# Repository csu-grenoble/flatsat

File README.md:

# Easy-Space Flatsat  📡 🚀 extensions

Extensions to [Easy Space](https://www.easy-space.fr/) INISAT flatsat mockup

## [Board #1: ThingSat @ INISAT](Hardware/Thingsat_INISAT)  📡 🚀 (OBC + LoRa Gateway + CAN Bus)

* 1x [ST Nucleo L432KC](https://www.st.com/en/evaluation-tools/nucleo-l432kc.html)
* 1x [RAK Wireless RAK5146 (all bands)](https://store.rakwireless.com/products/wislink-concentrator-module-sx1303-rak5146-lorawan?_pos=1&_sid=c9dc2f56d&_ss=r&variant=39667784908998)
* 1x Mikrobus slots for homebrew LoRa click boards (Lambda80, GNSS RTK) or [others click boards](https://www.mikroe.com/shop)
* 3x [Groove connectors](https://wiki.seeedstudio.com/Grove_System/)
* 1x [ST L9616 Automotive High Speed Can Bus Transceiver](https://www.st.com/en/automotive-analog-and-power/l9616.html)

## [Board #2 ESP32 TinyGS](Hardware/2U-PCB-TinyGS)

* 1x [ESP32 Wroom](https://www.espressif.com/en/products/devkits)
* 2x Mikrobus slots for homebrew LoRa click boards (Lambda80, RN2483) or [others click boards](https://www.mikroe.com/shop)
* 6x [Groove connectors](https://wiki.seeedstudio.com/Grove_System/)
* 1x [ST L9616 Automotive High Speed Can Bus Transceiver](https://www.st.com/en/automotive-analog-and-power/l9616.html)

See [TinyGS 2G4 Station](https://github.com/thingsat/tinygs_2g4station)

## Board #3 Nucleo L476RG

* 1x [Nucleo L476RG](https://www.st.com/en/evaluation-tools/nucleo-l476rg.html)
* 1x [ST L9616 Automotive High Speed Can Bus Transceiver](https://www.st.com/en/automotive-analog-and-power/l9616.html)

## References

* [EasySpace Diffusion](https://github.com/EasySpace-Diffusion)
* [TinyGS 2G4 Station](https://github.com/thingsat/tinygs_2g4station)

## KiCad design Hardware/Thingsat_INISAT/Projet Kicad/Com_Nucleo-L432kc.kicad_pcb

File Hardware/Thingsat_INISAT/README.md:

# **Carte Thingsat @ INISAT 📡 🚀 : OBC + Communication avec Nucleo L432KC + Gateway RAK5146**

La carte [Thingsat](https://gricad-gitlab.univ-grenoble-alpes.fr/thingsat/public/-/blob/master/README.md?ref_type=heads) @ INISAT a pour but de fonctionner comme un OBC qui peut se relier à l'environnement INISAT grace au header standardisé. 

Cette carte fonctionne également comme une carte de communication avancée LoRa/FSK avec l'ajout d'un module [gateway LoRa (+ GNSS) au format mini-PCIe](https://www.mikroe.com/mikrobus) comme le module [RAK5146](../../Hardware/sx1302_modules).

> Remarque: D'autres modules gateways LoRa avec ou sans module GNSS sont compatibles avec la carte. Voir la [liste](../../Hardware/sx1302_modules).

Cette carte peut accueillir un module MikroBus qui peut accueillir des platines de l'[écosystème Mikrobus](https://www.mikroe.com/mikrobus).

Cette carte peut accueillir trois platines Grove I2C situés sous le module mini-PCIe .

La carte [Thingsat](https://gricad-gitlab.univ-grenoble-alpes.fr/thingsat/public/-/blob/master/README.md?ref_type=heads) @ INISAT peut être utilisée seule (standalone) pour des expérimentations à bord de [ballons stratosphériques](https://gricad-gitlab.univ-grenoble-alpes.fr/thingsat/public/-/blob/master/balloons/README.md).

## Schématique

[Schematic](schematic.pdf)

## Firmware

Le firmware avec RIOT OS est disponible [ici](../../Software/riot).

Le firmware avec [ici](../../Software/arduino) est à l'étude.

## Montages

La carte peut être montée en deux versions:

**Carte avec 1 connecteur mini-PCI-Express (pour accueillir un concentrateur LoRa) et 1 support Mikrobus**

**Carte avec 3 connecteurs Grove et 1 support Mikrobus**

## OpenLog

Pour journaliser la console d'exécution du firmware de la carte Nucleo L432KC, vous pouvez ajouter une [platine OpenLog](https://github.com/CampusIoT/tutorial/tree/master/openlogger) sur les headers externes de la carte.

| OpenLog | Nucleo L432KC |
| ------- | ------------- |
| `3V3` | `3V3` (et non `VIN`) |
| `GND` | `GND` |
| `RXI` | `A7` (aka `UART2_TX`) | 

> NB: il est recommandé que le port console soit configuré à 9600 bauds pour éviter la perte de caratères lors de l'écriture sur la carte SD. Pour les firmwares avec RIOT OS, il faut redéfinir dans le Makefile `STDIO_UART_BAUDRATE` avec `CFLAGS += -DSTDIO_UART_BAUDRATE=9600`

## Description de la carte
La carte est equipée de:

 - Un emplacement pour carte **Nucleo-32** (ou arduino nano)
 - Un emplacement **MikroBus**
 - Un connecteur **mini-PCI-Express** OU 3 connecteurs **Grove** I2C (en fonction de la version de la carte)
 - Un connecteur **Inisat** (pour se raccorder aux autres cartes de l'ecosystème Inisat)
 - Un **transceiver CAN** ([L9616](https://www.st.com/en/automotive-analog-and-power/l9616.html) - STMicroelectronics)
 - Un **capteur de température** I2C ([MCP9808](https://www.microchip.com/en-us/product/mcp9808#document-table) - Microchip)

## Nucleo 32 (L432KC)

## Emplacement MikroBus

## Connecteur mini PCI Express

## [Modules SX1302/3 compatibles](../sx1302_modules)

* [x] RAK5146 Gateway Concentrator Module for LoRaWAN SPI
* [ ] RAK2287 WisLink LPWAN Concentrator SPI (to test)
* [x] Nebra NBR-0094
* [x] Seeedstudio Wio-WM1303 Long Range Gateway Module
* [ ] Seeedstudio Wio-WM1302 Long Range Gateway Module  (to test)
* [ ] Heltec HT1303  (to test)

## Jumpers de selection des signaux

Les signaux marqués d'une étoile sur les diagrammes sont partagées entre plusieurs empreintes.
Pour pouvoir utiliser ces signaux il faut donc les "router" vers l'emplacement dont on veut se servir en plaçant correctement les jumpers en bas à droite de la carte.

- PWM1 : 
	- position haute: `PWM Mikrobus` 	(pin 8 de l'empreinte Mikrobus)
	- position basse: `PWM Inisat` 		(pin 6 du connecteur Inisat)
	
- INT :
	- position haute: `INT Mikrobus` 	(pin 7 de l'empreinte Mikrobus)
	- position basse: `PPS Lora core` 	(pin 19 du connecteur mini PCI Express)
	
- UART (Rx et Tx) :
	- position haute: `UART Mikrobus` 	(pin 5 et 6 de l'empreinte Mikrobus)
	- position basse: `UART GPS Lora core` (pin 31 et 33 du connecteur mini PCI Express)

## Transceiver CAN

Le transceiver CAN peut être configuré pour opérations à hautes vitesses (> 250KBaud/s) ou à basse vitesse (< 250KBaud/s).
Pour positionner le transceiver en mode haute vitesse, il faut placer un jumper sur le connecteur `JP2`.

## Capteur de temperature [MPC9808](https://www.microchip.com/en-us/product/mcp9808#document-table)

L'adresse i2c du capteur de température est définie comme suit : `0b 0 0 1 1 A2 A1 A0`
les bits de poids faibles A2,A1 et A0 sont définis en plaçant des résistances 0 Ohms (_il ne faut donc placer qu'une seule résistance pour chaque bit_): 

## Modularité de la carte

Les composants entourés d'un rectangle en pointillé ne doivent pas necessairement être montées. Cela dépend de l'usage de la carte. Voici les composants concernés:

* Alimentation Nucleo
	* `R7`: alimentation de la nucleo en 5V (_nécessaire si la carte Inisat est utilisé seule **ET** que l'on a besoin d'utiliser le 5V pour le Mikrobus_)
	* `R6`: alimentation de la nucleo en 3.3V (_nécessaire si la carte Inisat est utilisé seule_)
* Alimentation Transceiver CAN
	* `R9`: alimentation L9616 en 5V
	* `R8`: alimentation L9616 en 3.3V (_par défaut_)
* Selection adresse i2c capteur de temperature (`R10`-`R15`)
	* [voir ci-dessus](#capteur-de-temperature)

# Contributeurs

* Léo CORDIER (Design PCB + montage)
* Vincent Grennerat (Design PCB)
* Didier Donsez (firmware de test)
* [Lucas ORLANDO BERNARDES](https://www.linkedin.com/in/lucas-orlando-bernardes-1b7397256/) (initial design)

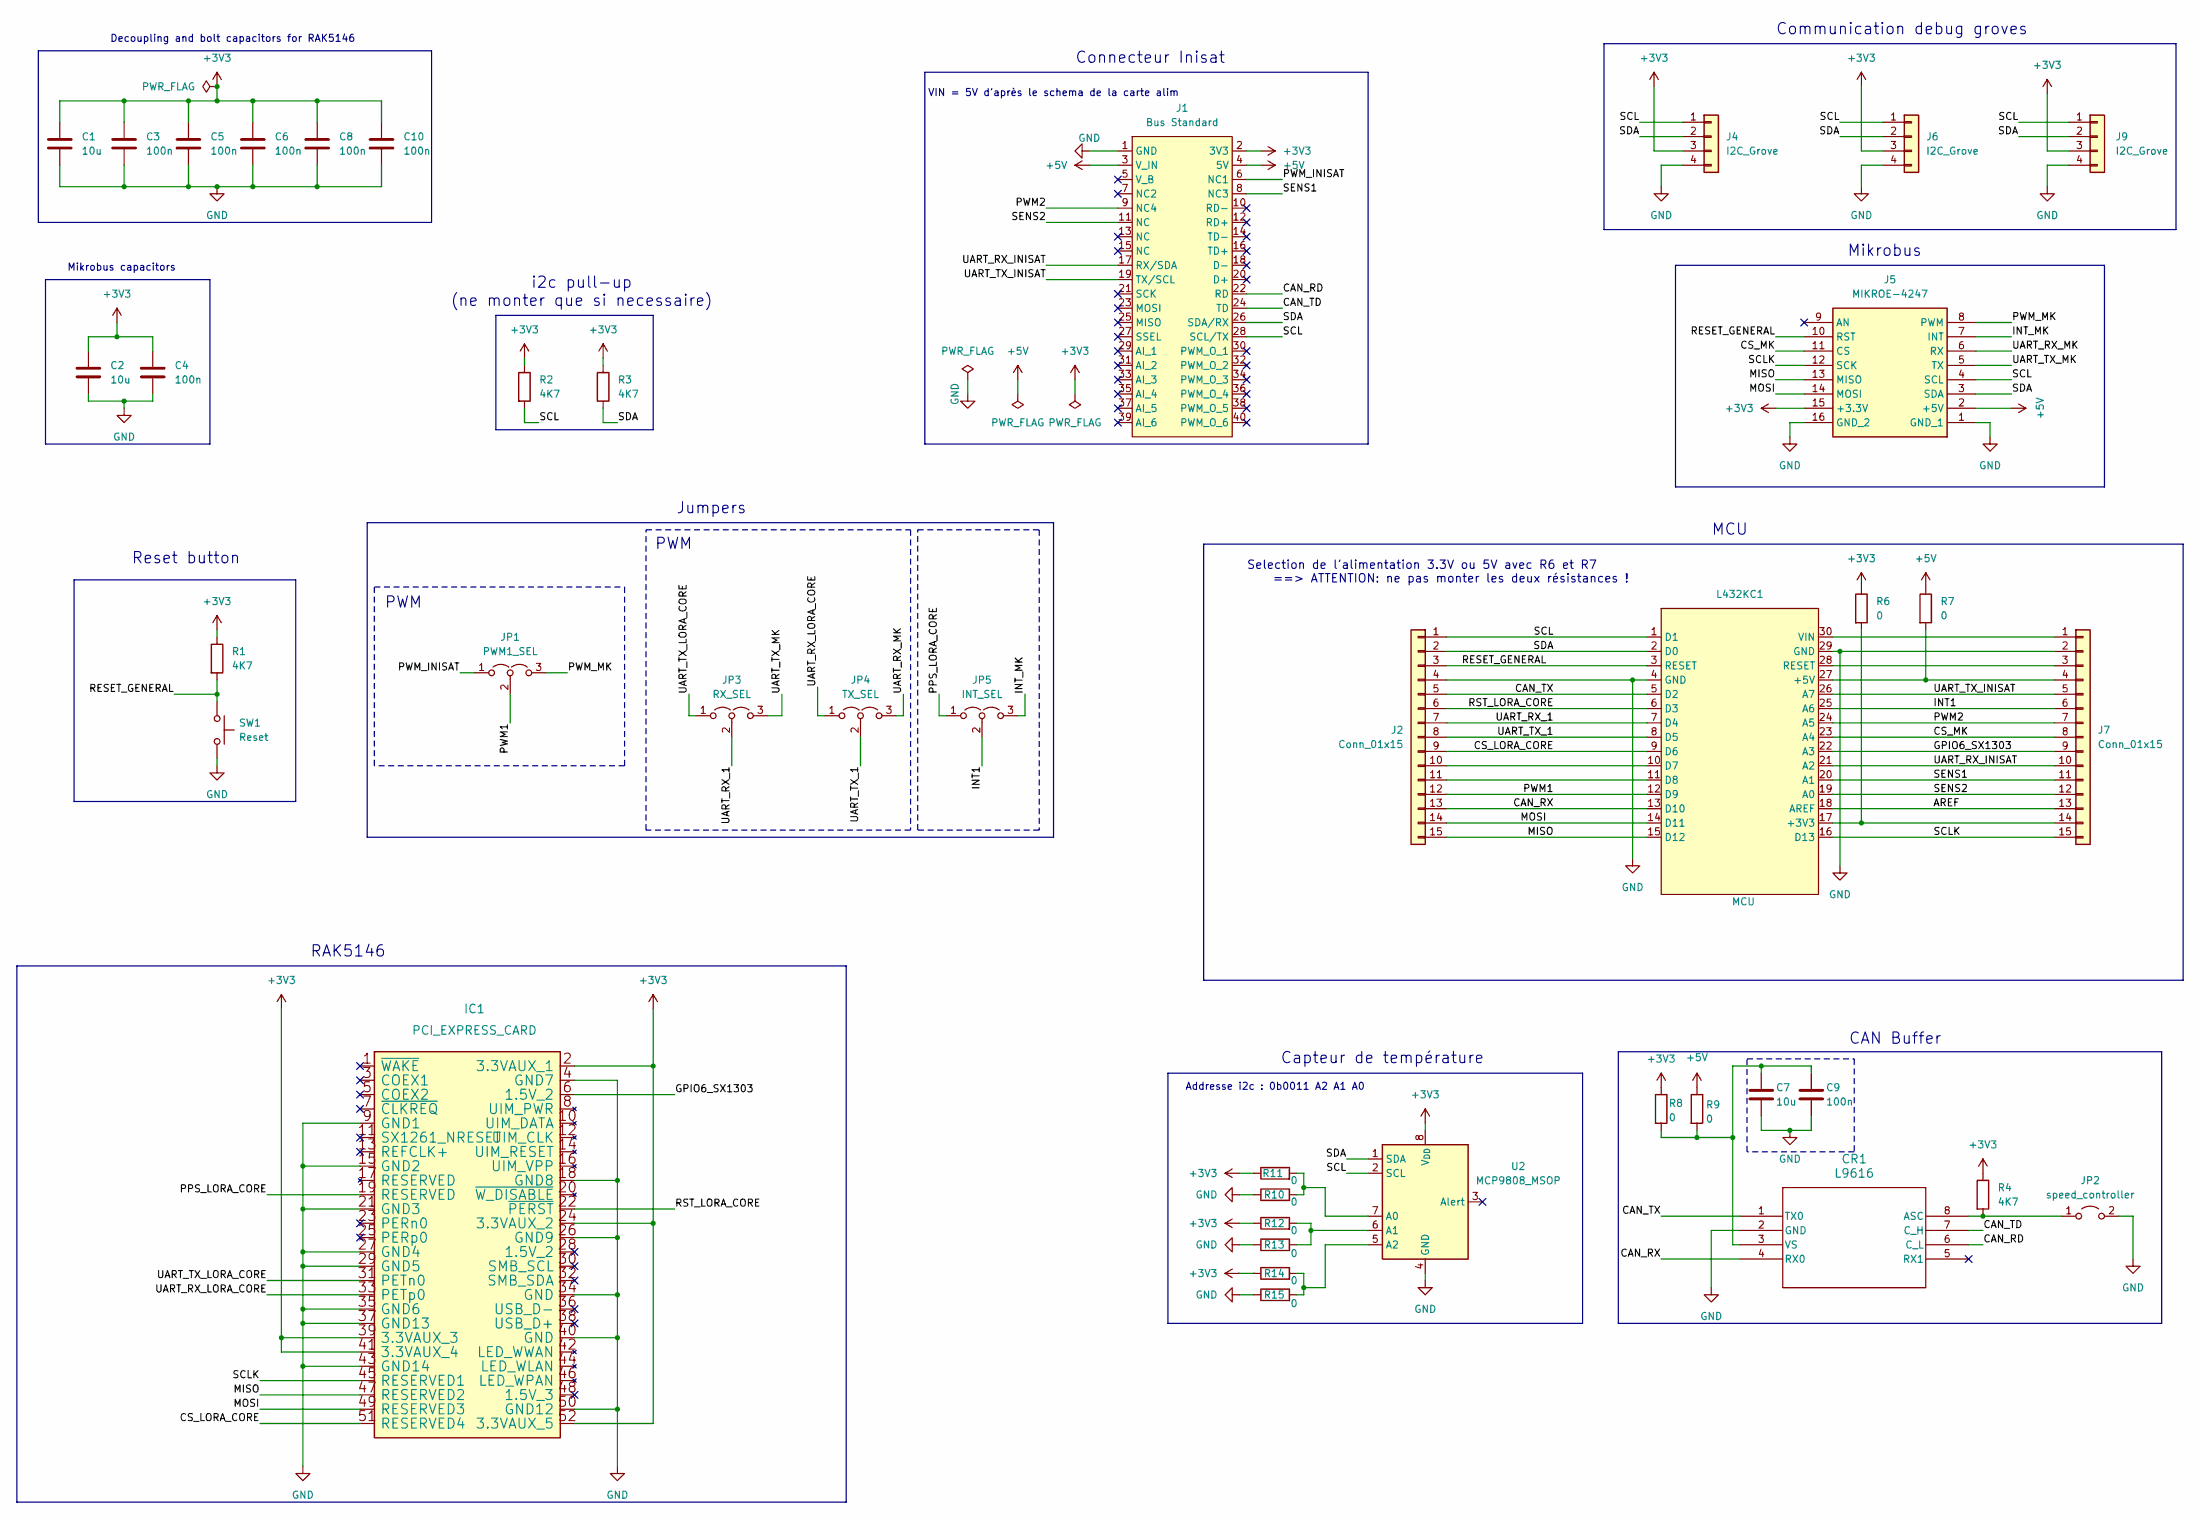
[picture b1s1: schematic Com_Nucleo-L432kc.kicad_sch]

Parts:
C1, C2, C7: 10u; C_0805_2012Metric_Pad1.18x1.45mm_HandSolder
C3, C4, C5, C6, C8, C9, C10: 100n; C_0805_2012Metric_Pad1.18x1.45mm_HandSolder
CR1: L9616; SO-8_3.9x4.9mm_P1.27mm
IC1: PCI_EXPRESS_CARD; BUS_PCI_Express_Mini
J1: Bus Standard; flatsat_conn
J2, J7: Conn_01x15; PinHeader_1x15_P2.54mm_Vertical
J4, J6, J9: I2C_Grove; NS-Tech_Grove_1x04_P2mm_Vertical
J5: MIKROE-4247; MIKROE4247; Manufacturer_Part_Number MIKROE-4247; Mouser Part Number 932-MIKROE-4247
JP1: PWM1_SEL; PinHeader_1x03_P2.54mm_Vertical
JP2: speed_controller; PinHeader_1x02_P2.54mm_Vertical
JP3: RX_SEL; PinHeader_1x03_P2.54mm_Vertical
JP4: TX_SEL; PinHeader_1x03_P2.54mm_Vertical
JP5: INT_SEL; PinHeader_1x03_P2.54mm_Vertical
L432KC1: MCU; Arduino_Nano
R1, R2, R3, R4: 4K7; R_0805_2012Metric_Pad1.20x1.40mm_HandSolder
R6, R7, R8, R9, R10, R11, R12, R13, R14, R15: 0; R_0805_2012Metric_Pad1.20x1.40mm_HandSolder
SW1: Reset; SW_PUSH_6mm
U2: MCP9808_MSOP; MSOP-8_3x3mm_P0.65mm

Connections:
+3V3: C1.1, C2.1, C3.1, C4.1, C5.1, C6.1, C8.1, C10.1, IC1.2 (3.3VAUX_1), IC1.24 (3.3VAUX_2), IC1.39 (3.3VAUX_3), IC1.41 (3.3VAUX_4), IC1.52 (3.3VAUX_5), J1.2 (3V3), J4.3, J5.15 (+3.3V), J6.3, J9.3, R1.1, R2.1, R3.1, R4.1, R6.1, R8.1, R11.1, R12.1, R14.1, U2.8 (V_{DD})
+5V: J1.3 (V_IN), J1.4 (5V), J5.2 (+5V), R7.1, R9.1
/AREF: J7.13, L432KC1.18 (AREF)
/CAN_RD: CR1.6 (C_L), J1.22 (RD)
/CAN_RX: CR1.4 (RX0), J2.13, L432KC1.13 (D10)
/CAN_TD: CR1.7 (C_H), J1.24 (TD)
/CAN_TX: CR1.1 (TX0), J2.5, L432KC1.5 (D2)
/CS_LORA_CORE: IC1.51 (RESERVED4), J2.9, L432KC1.9 (D6)
/CS_MK: J5.11 (CS), J7.8, L432KC1.23 (A4)
/GPIO6_SX1303: IC1.6 (1.5V_2), J7.9, L432KC1.22 (A3)
/INT1: J7.6, JP5.2 (C), L432KC1.25 (A6)
/INT_MK: J5.7 (INT), JP5.3 (B)
/MISO: IC1.47 (RESERVED2), J2.15, J5.13 (MISO), L432KC1.15 (D12)
/MOSI: IC1.49 (RESERVED3), J2.14, J5.14 (MOSI), L432KC1.14 (D11)
/PPS_LORA_CORE: IC1.19 (RESERVED), JP5.1 (A)
/PWM1: J2.12, JP1.2 (C), L432KC1.12 (D9)
/PWM2: J1.9 (NC4), J7.7, L432KC1.24 (A5)
/PWM_INISAT: J1.6 (NC1), JP1.1 (A)
/PWM_MK: J5.8 (PWM), JP1.3 (B)
/RESET_GENERAL: J2.3, J5.10 (RST), L432KC1.3 (RESET), R1.2, SW1.1
/RST_LORA_CORE: IC1.22 (~PERST), J2.6, L432KC1.6 (D3)
/SCL: J1.28 (SCL/TX), J2.1, J4.1, J5.4 (SCL), J6.1, J9.1, L432KC1.1 (D1), R2.2, U2.2 (SCL)
/SCLK: IC1.45 (RESERVED1), J5.12 (SCK), J7.15, L432KC1.16 (D13)
/SDA: J1.26 (SDA/RX), J2.2, J4.2, J5.3 (SDA), J6.2, J9.2, L432KC1.2 (D0), R3.2, U2.1 (SDA)
/SENS1: J1.8 (NC3), J7.11, L432KC1.20 (A1)
/SENS2: J1.11 (NC), J7.12, L432KC1.19 (A0)
/UART_RX_1: J2.7, JP3.2 (C), L432KC1.7 (D4)
/UART_RX_INISAT: J1.17 (RX/SDA), J7.10, L432KC1.21 (A2)
/UART_RX_LORA_CORE: IC1.33 (PETp0), JP4.1 (A)
/UART_RX_MK: J5.6 (RX), JP4.3 (B)
/UART_TX_1: J2.8, JP4.2 (C), L432KC1.8 (D5)
/UART_TX_INISAT: J1.19 (TX/SCL), J7.5, L432KC1.26 (A7)
/UART_TX_LORA_CORE: IC1.31 (PETn0), JP3.1 (A)
/UART_TX_MK: J5.5 (TX), JP3.3 (B)
GND: C1.2, C2.2, C3.2, C4.2, C5.2, C6.2, C7.2, C8.2, C9.2, C10.2, CR1.2 (GND), IC1.4 (GND7), IC1.9 (GND1), IC1.15 (GND2), IC1.18 (GND8), IC1.21 (GND3), IC1.26 (GND9), IC1.27 (GND4), IC1.29 (GND5), IC1.34 (GND), IC1.35 (GND6), IC1.37 (GND13), IC1.40 (GND), IC1.43 (GND14), IC1.50 (GND12), J1.1 (GND), J2.4, J4.4, J5.1 (GND_1), J5.16 (GND_2), J6.4, J7.2, J9.4, JP2.2 (B), L432KC1.4 (GND), L432KC1.29 (GND), R10.1, R13.1, R15.1, SW1.2, U2.4 (GND)
unnamed: CR1.8 (ASC), JP2.1 (A), R4.2
unnamed: C7.1, C9.1, CR1.3 (VS), R8.2, R9.2
unnamed: J2.10, L432KC1.10 (D7)
unnamed: J2.11, L432KC1.11 (D8)
unnamed: J7.1, L432KC1.30 (VIN)
unnamed: J7.3, L432KC1.28 (RESET)
unnamed: J7.4, L432KC1.27 (+5V), R7.2
unnamed: J7.14, L432KC1.17 (+3V3), R6.2
unnamed: R10.2, R11.2, U2.7 (A0)
unnamed: R12.2, R13.2, U2.6 (A1)
unnamed: R14.2, R15.2, U2.5 (A2)

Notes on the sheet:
Connecteur Inisat
Capteur de température
RAK5146
PWM
VIN = 5V d'après le schema de la carte alim
Selection de l'alimentation 3.3V ou 5V avec R6 et R7 ==> ATTENTION: ne pas monter les deux résistances !
Mikrobus capacitors
Communication debug groves
Addresse i2c : 0b0011 A2 A1 A0
Mikrobus
MCU
CAN Buffer
Jumpers
Decoupling and bolt capacitors for RAK5146
i2c pull-up (ne monter que si necessaire)
Reset button

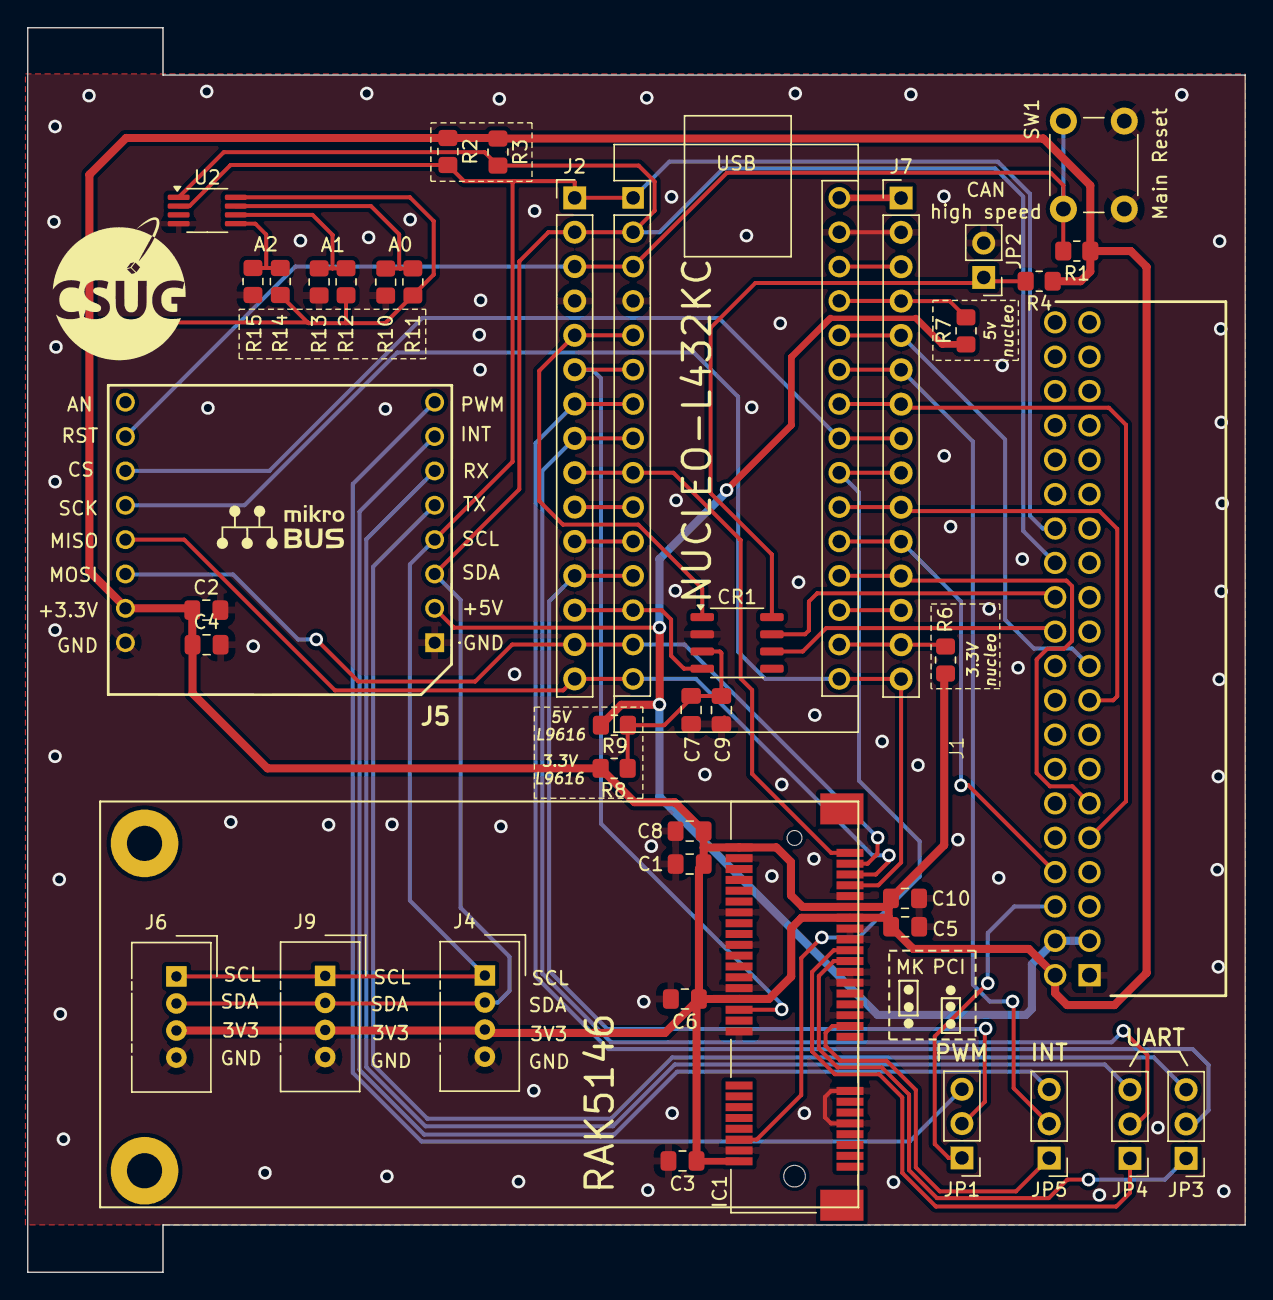
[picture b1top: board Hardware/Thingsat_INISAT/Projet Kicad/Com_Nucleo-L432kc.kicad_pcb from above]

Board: 2 copper layers, 90.0 x 92.0 mm, 42 parts (1 on the bottom side), 46 nets.

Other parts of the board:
QR: LOGO; qr_code_flatsat

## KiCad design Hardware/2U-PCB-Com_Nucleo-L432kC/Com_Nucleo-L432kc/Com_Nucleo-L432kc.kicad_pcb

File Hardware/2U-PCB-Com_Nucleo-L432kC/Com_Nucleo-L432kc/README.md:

# **Carte Thingsat @ INISAT 📡 🚀 : OBC + Communication avec Nucleo L432KC + Gateway RAK5146**

La carte [Thingsat](https://gricad-gitlab.univ-grenoble-alpes.fr/thingsat/public/-/blob/master/README.md?ref_type=heads) @ INISAT a pour but de fonctionner comme un OBC qui peut se relier à l'environnement INISAT grace au header standardisé. 

Cette carte peut accueillir un module MikroBus, trois modules Grove et une gateway LoRa RAK156 (+ GNSS).

> Remarque: D'autres modules gateways LoRa sont compatibles avec la carte. Voir la [liste](../../sx1302_modules).

Le firmware sur RIOT OS est disponible [ici](../../Software/riot).

Dotée du module gateway LoRa RAK156, elle peut également être utilisée comme la carte [Thingsat](https://gricad-gitlab.univ-grenoble-alpes.fr/thingsat/public/-/blob/master/README.md?ref_type=heads) @ INISAT.

La carte peut être montée en deux versions:

**Carte avec 1 connecteur mini-PCI-Express (pour accueillir un concentrateur LoRa) et 1 support Mikrobus**

**Carte avec 3 connecteurs Grove et 1 support Mikrobus**

## Description de la carte
La carte est equipée de:

 - Un emplacement pour carte **Nucleo-32** (ou arduino nano)
 - Un emplacement **MikroBus**
 - Un connecteur **mini-PCI-Express** OU 3 connecteurs **Grove** I2C (en fonction de la version de la carte)
 - Un connecteur **Inisat** (pour se raccorder aux autres cartes de l'ecosystème Inisat)
 - Un **transceiver CAN** ([L9616](https://www.st.com/en/automotive-analog-and-power/l9616.html) - STMicroelectronics)
 - Un **capteur de température** I2C ([MCP9808](https://www.microchip.com/en-us/product/mcp9808#document-table) - Microchip)

## Nucleo 32 (L432KC)

## Emplacement MikroBus

## mini PCI Express

## Jumpers de selection des signaux
Les signaux marqués d'une étoile sur les diagrammes sont partagées entre plusieurs empreintes.
Pour pouvoir utiliser ces signaux il faut donc les "router" vers l'emplacement dont on veut se servir en plaçant correctement les jumpers en bas à droite de la carte.

- PWM1 : 
	- position haute: `PWM Mikrobus` 		(pin 8 de l'empreinte Mikrobus)
	- position basse: `PWM Inisat` 		(pin 6 du connecteur Inisat)
	
- INT :
	- position haute: `INT Mikrobus` 		(pin 7 de l'empreinte Mikrobus)
	- position basse: `PPS Lora core` 	(pin 19 du connecteur mini PCI Express)
	
- UART (Rx et Tx) :
	- position haute: `UART Mikrobus` 	(pin 5 et 6 de l'empreinte Mikrobus)
	- position basse: `UART GPS Lora core` (pin 31 et 33 du connecteur mini PCI Express)

## Transceiver CAN
Le transceiver CAN peut être configuré pour opérations à hautes vitesses (> 250KBaud/s) ou à basse vitesse (< 250KBaud/s).
Pour positionner le transceiver en mode haute vitesse, il faut placer un jumper sur le connecteur `JP2`.

## Capteur de temperature
L'adresse i2c du capteur de température est définie comme suit : `0b 0 0 1 1 A2 A1 A0`
les bits de poids faibles A2,A1 et A0 sont définis en plaçant des résistances 0 Ohms (_il ne faut donc placer qu'une seule résistance pour chaque bit_): 

## Modularité de la carte
Les composants entourés d'un rectangle en pointillé ne doivent pas necessairement être montées. Cela dépend de l'usage de la carte. Voici les composants concernés:

* Alimentation Nucleo
	* `R7`: alimentation de la nucleo en 5V (_nécessaire si la carte Inisat est utilisé seule **ET** que l'on a besoin d'utiliser le 5V pour le Mikrobus_)
	* `R6`: alimentation de la nucleo en 3.3V (_nécessaire si la carte Inisat est utilisé seule_)
* Alimentation Transceiver CAN
	* `R9`: alimentation L9616 en 5V
	* `R8`: alimentation L9616 en 3.3V (_par défaut_)
* Selection adresse i2c capteur de temperature (`R10`-`R15`)
	* [voir ci-dessus](#capteur-de-temperature)

# Contributeurs

* Léo CORDIER (Design PCB + montage)
* Vincent Grennerat (Design PCB)
* Didier Donsez (firmware de test)

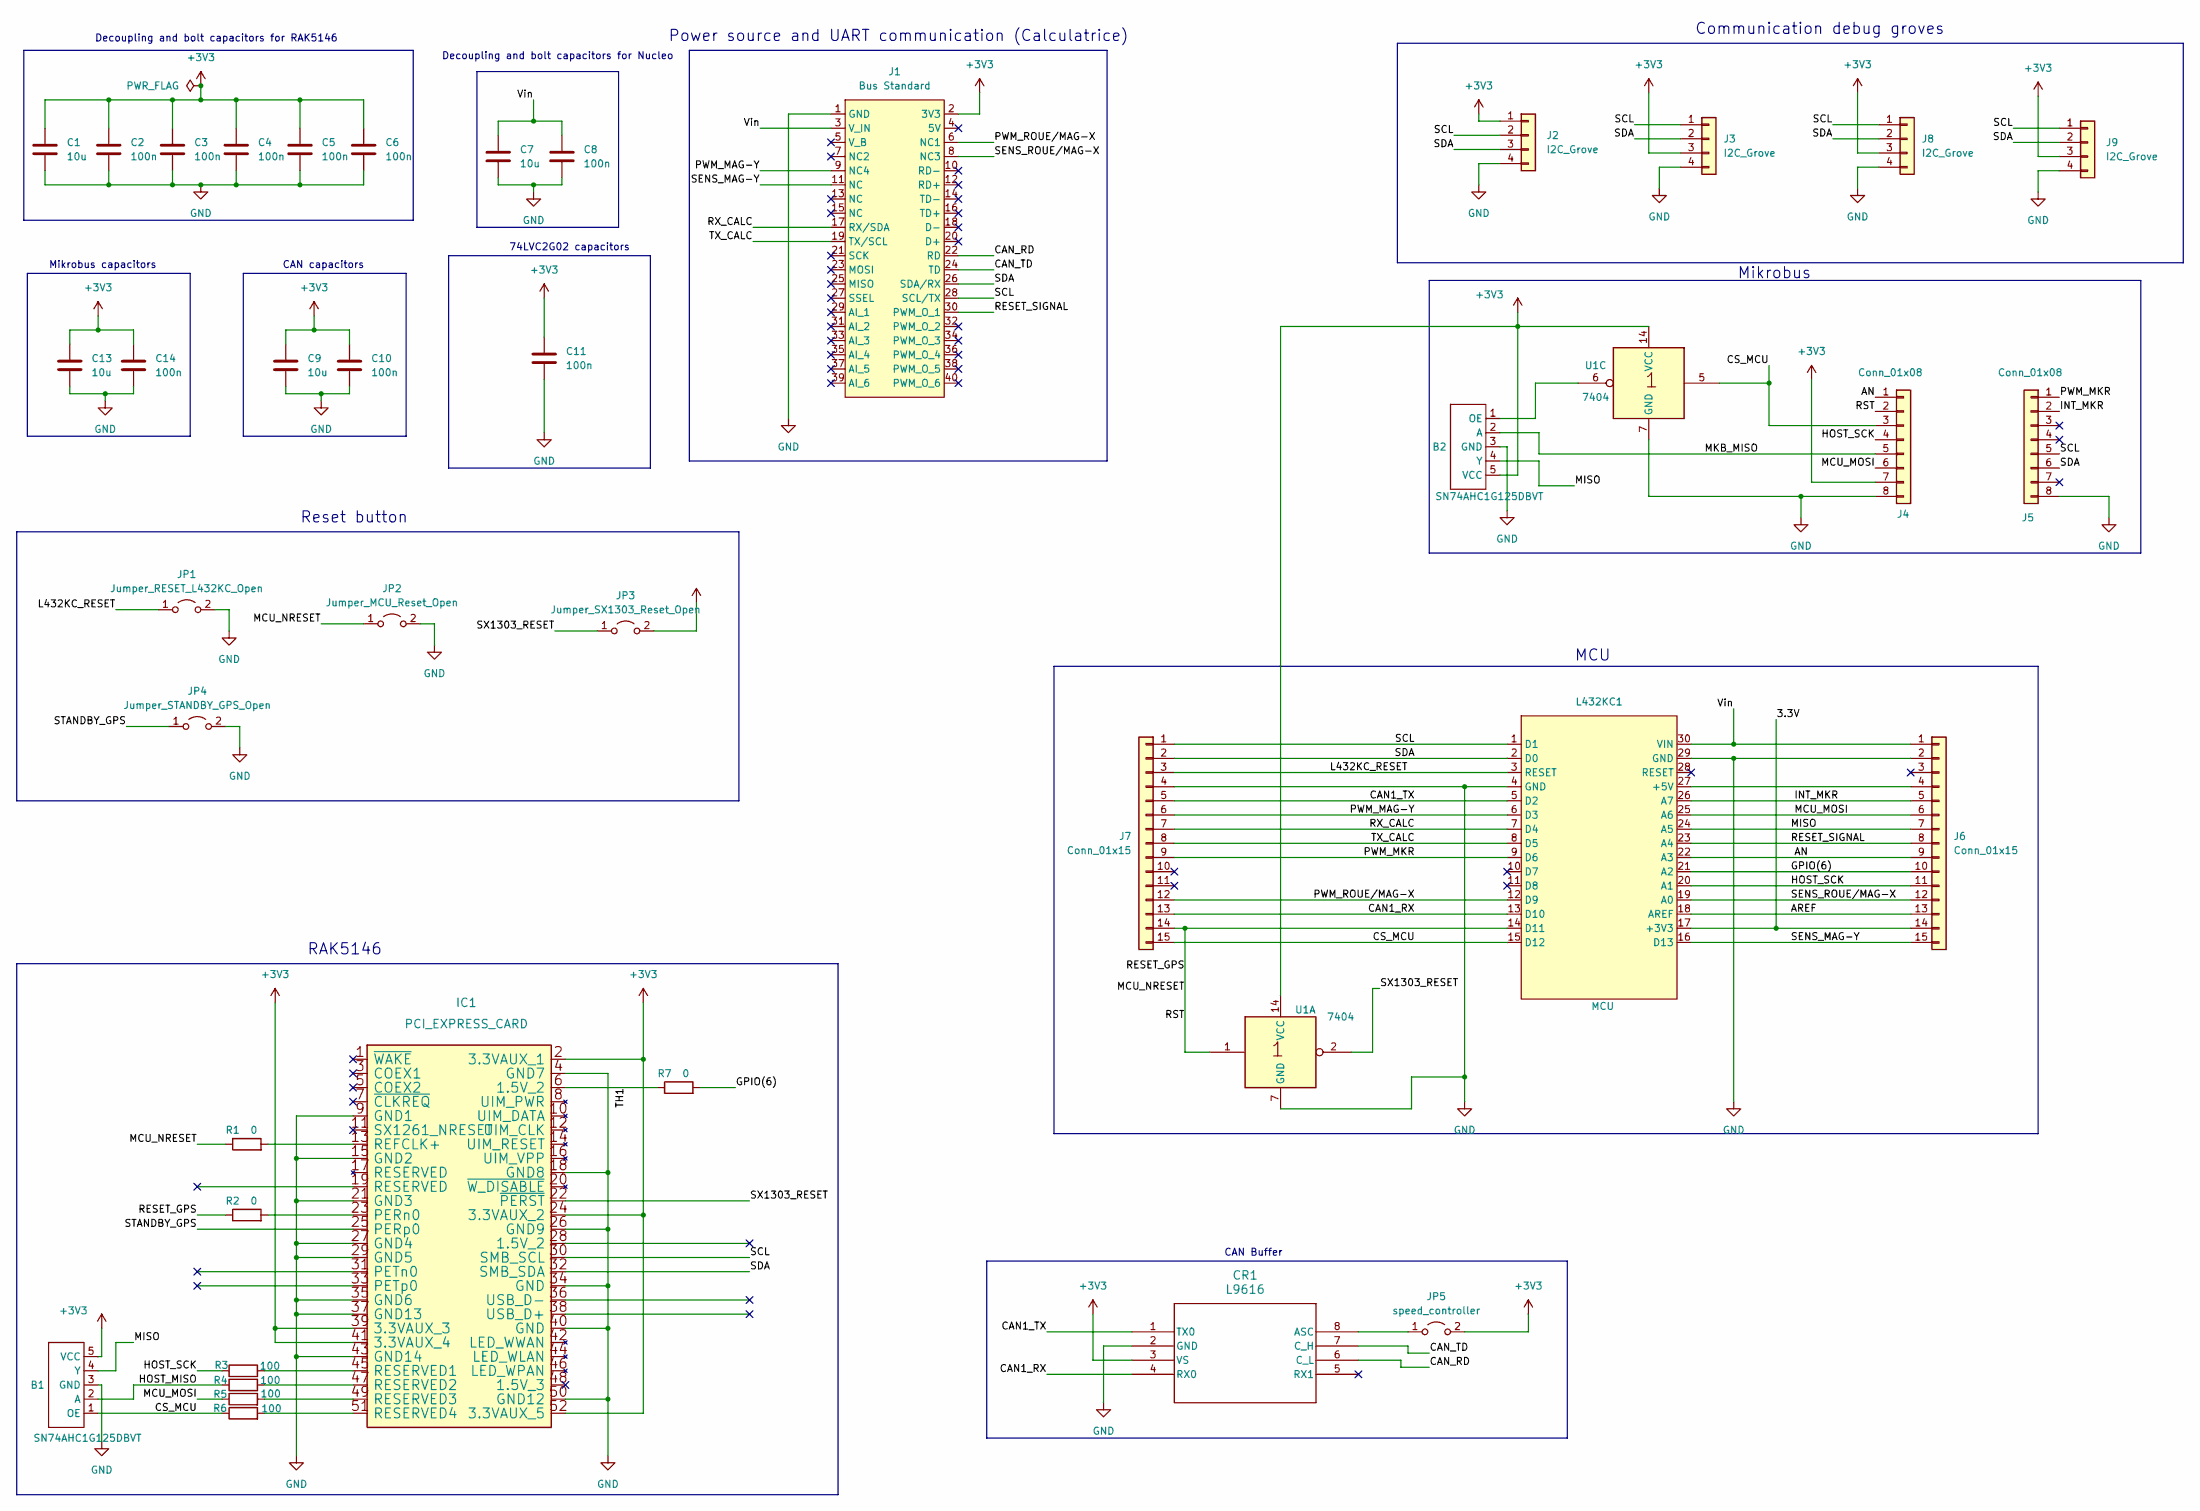
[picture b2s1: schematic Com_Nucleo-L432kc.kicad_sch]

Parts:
B1, B2: SN74AHC1G125DBVT; TSOP-5_1.65x3.05mm_P0.95mm
C1, C7, C9, C13: 10u; C_0805_2012Metric
C2, C3, C4, C5, C6, C8, C10, C11, C14: 100n; C_0805_2012Metric
CR1: L9616; SO-8_STM
IC1: PCI_EXPRESS_CARD; BUS_PCI_Express_Mini
J1: Bus Standard; flatsat_conn
J2: I2C_Grove; PinSocket_1x04_P2.54mm_Vertical
J3, J8, J9: I2C_Grove; NS-Tech_Grove_1x04_P2mm_Vertical
J4, J5: Conn_01x08; MIkrobus_Connector
J6, J7: Conn_01x15; PinSocket_1x15_P2.54mm_Vertical
JP1: Jumper_RESET_L432KC_Open; SW_Push_1P1T_NO_CK_KMR2
JP2: Jumper_MCU_Reset_Open; SW_Push_1P1T_NO_CK_KMR2
JP3: Jumper_SX1303_Reset_Open; SW_Push_1P1T_NO_CK_KMR2
JP4: Jumper_STANDBY_GPS_Open; PinHeader_1x02_P2.54mm_Vertical
JP5: speed_controller; PinHeader_1x02_P2.54mm_Vertical
L432KC1: MCU; Arduino_Nano
R1, R2, R7: 0; R_0805_2012Metric
R3, R4, R5, R6: 100; R_0805_2012Metric
U1: 7404; N14

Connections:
+3V3: B1.5 (VCC), B2.5 (VCC), C1.1, C2.1, C3.1, C4.1, C5.1, C6.1, C9.1, C10.1, C11.1, C13.1, C14.1, CR1.3 (VS), IC1.2 (3.3VAUX_1), IC1.24 (3.3VAUX_2), IC1.39 (3.3VAUX_3), IC1.41 (3.3VAUX_4), IC1.52 (3.3VAUX_5), J1.2 (3V3), J2.1, J3.3, J4.7, J8.3, J9.3, JP5.2 (B), U1.14 (VCC); also elsewhere on the board
/3.3V: J6.14, L432KC1.17 (+3V3)
/AN: J4.1, J6.9, L432KC1.22 (A3)
/AREF: J6.13, L432KC1.18 (AREF)
/CAN1_RX: CR1.4 (RX0), J7.13, L432KC1.13 (D10)
/CAN1_TX: CR1.1 (TX0), J7.5, L432KC1.5 (D2)
/CAN_RD: CR1.6 (C_L), J1.22 (RD)
/CAN_TD: CR1.7 (C_H), J1.24 (TD)
/CS_MCU: B1.1 (OE), J4.3, J7.15, L432KC1.15 (D12), R6.1, U1.5
/GPIO(6): J6.10, L432KC1.21 (A2), R7.2
/HOST_MISO: B1.2 (A), R4.1
/HOST_SCK: J4.4, J6.11, L432KC1.20 (A1), R3.1
/INT_MKR: J5.2, J6.5, L432KC1.26 (A7)
/L432KC_RESET: J7.3, JP1.1 (A), L432KC1.3 (RESET); also elsewhere on the board
/MCU_MOSI: J4.6, J6.6, L432KC1.25 (A6), R5.1
/MCU_NRESET: J4.2, J7.14, JP2.1 (A), L432KC1.14 (D11), R1.1, R2.1, U1.1; also elsewhere on the board
/MISO: B1.4 (Y), B2.4 (Y), J6.7, L432KC1.24 (A5)
/MKB_MISO: B2.2 (A), J4.5
/PWM_MAG-Y: J1.9 (NC4), J7.6, L432KC1.6 (D3)
/PWM_MKR: J5.1, J7.9, L432KC1.9 (D6)
/PWM_ROUE/MAG-X: J1.6 (NC1), J7.12, L432KC1.12 (D9)
/RESET_SIGNAL: J1.30 (PWM_O_1), J6.8, L432KC1.23 (A4)
/RX_CALC: J1.17 (RX/SDA), J7.7, L432KC1.7 (D4)
/SCL: IC1.30 (SMB_SCL), J1.28 (SCL/TX), J2.2, J3.1, J5.5, J7.1, J8.1, J9.1, L432KC1.1 (D1)
/SDA: IC1.32 (SMB_SDA), J1.26 (SDA/RX), J2.3, J3.2, J5.6, J7.2, J8.2, J9.2, L432KC1.2 (D0)
/SENS_MAG-Y: J1.11 (NC), J6.15, L432KC1.16 (D13)
/SENS_ROUE/MAG-X: J1.8 (NC3), J6.12, L432KC1.19 (A0)
/STANDBY_GPS: IC1.25 (PERp0), JP4.1 (A)
/SX1303_RESET: IC1.22 (~PERST), JP3.1 (A), U1.2; also elsewhere on the board
/TH1: IC1.6 (1.5V_2), R7.1
/TX_CALC: J1.19 (TX/SCL), J7.8, L432KC1.8 (D5)
/Vin: C7.1, C8.1, J1.3 (V_IN), J6.1, L432KC1.30 (VIN)
GND: B1.3 (GND), B2.3 (GND), C1.2, C2.2, C3.2, C4.2, C5.2, C6.2, C7.2, C8.2, C9.2, C10.2, C11.2, C13.2, C14.2, CR1.2 (GND), IC1.4 (GND7), IC1.9 (GND1), IC1.15 (GND2), IC1.18 (GND8), IC1.21 (GND3), IC1.26 (GND9), IC1.27 (GND4), IC1.29 (GND5), IC1.34 (GND), IC1.35 (GND6), IC1.37 (GND13), IC1.40 (GND), IC1.43 (GND14), IC1.50 (GND12), J1.1 (GND), J2.4, J3.4, J4.8, J5.8, J6.2, J7.4, J8.4, J9.4, JP4.2 (B), L432KC1.4 (GND), L432KC1.29 (GND), U1.7 (GND); also elsewhere on the board
unnamed: B2.1 (OE), U1.6
unnamed: CR1.8 (ASC), JP5.1 (A)
unnamed: IC1.23 (PERn0), R2.2
unnamed: IC1.13 (REFCLK+), R1.2
unnamed: IC1.45 (RESERVED1), R3.2
unnamed: IC1.47 (RESERVED2), R4.2
unnamed: IC1.49 (RESERVED3), R5.2
unnamed: IC1.51 (RESERVED4), R6.2
unnamed: J6.4, L432KC1.27 (+5V)

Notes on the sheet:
74LVC2G02 capacitors
Power source and UART communication (Calculatrice)
Decoupling and bolt capacitors for Nucleo
RAK5146
Mikrobus capacitors
Communication debug groves
Mikrobus
MCU
CAN Buffer
Decoupling and bolt capacitors for RAK5146
CAN capacitors
Reset button

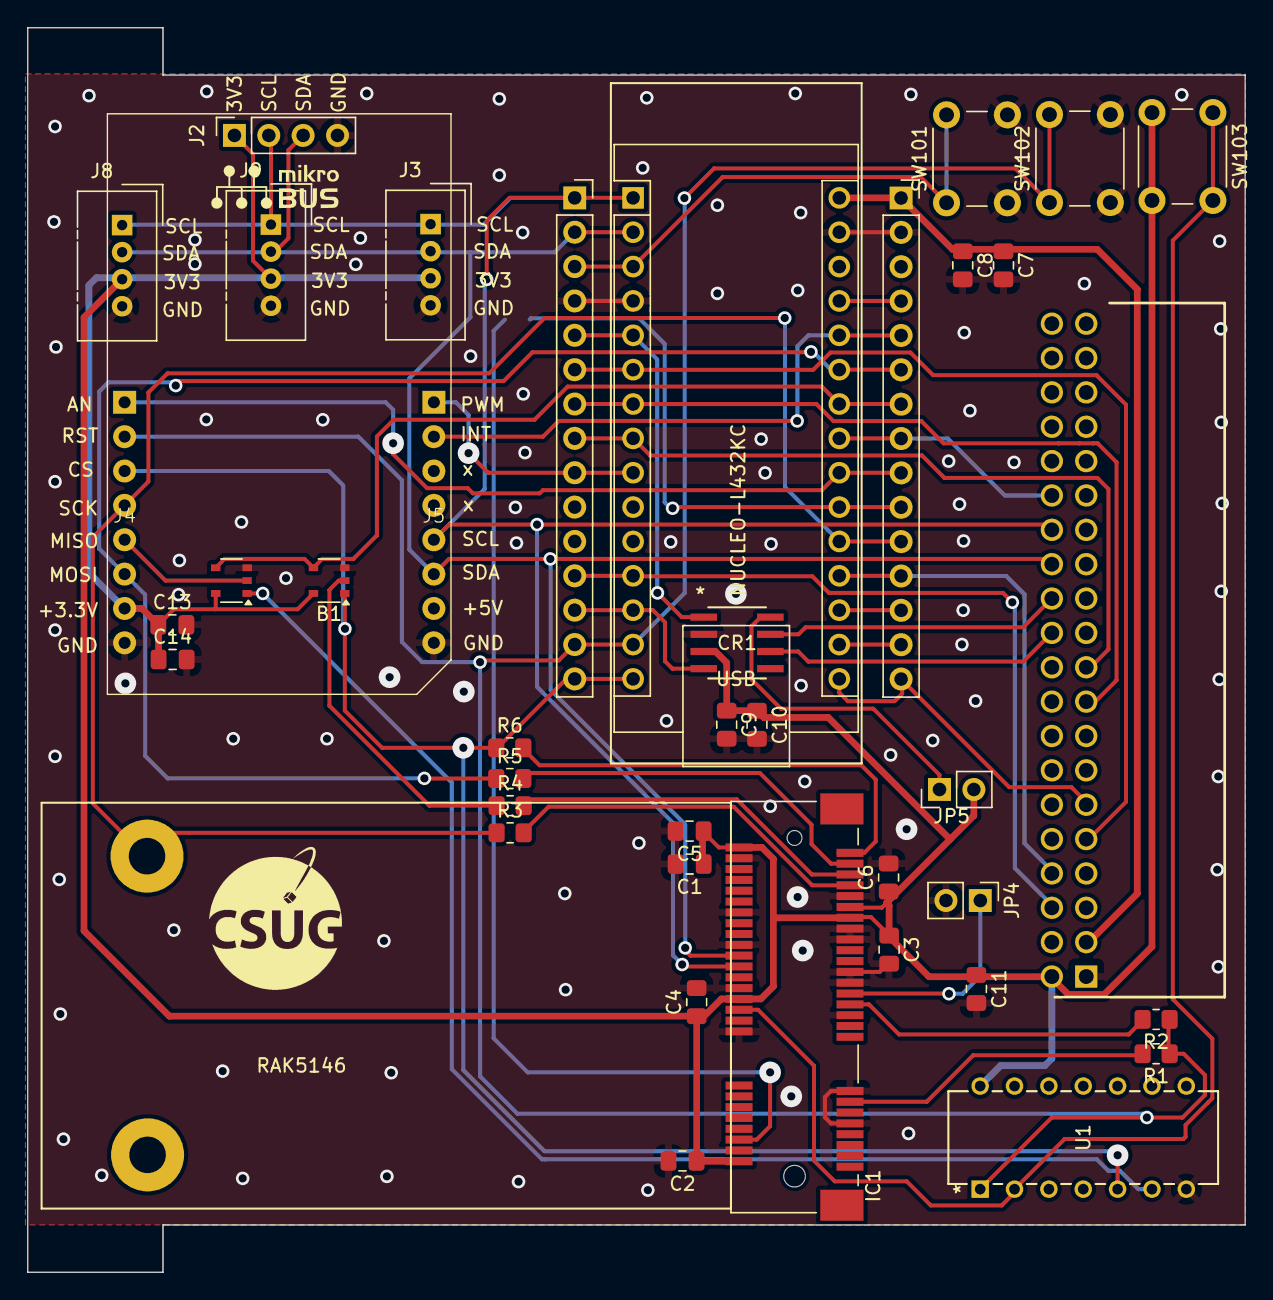
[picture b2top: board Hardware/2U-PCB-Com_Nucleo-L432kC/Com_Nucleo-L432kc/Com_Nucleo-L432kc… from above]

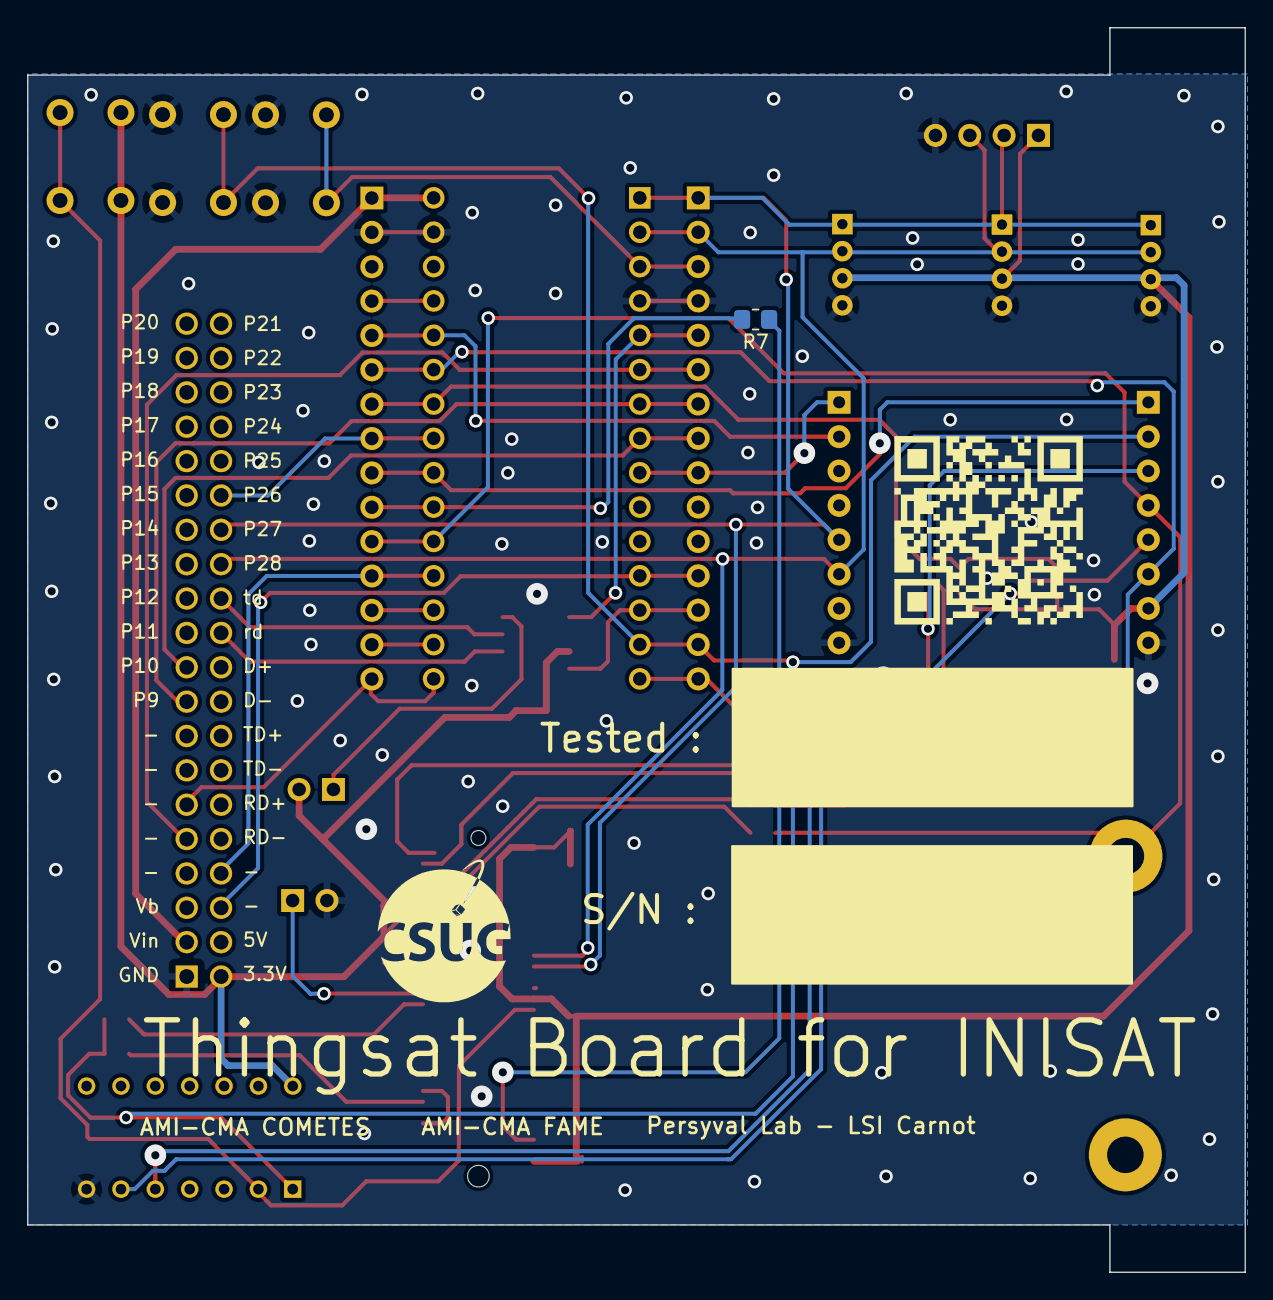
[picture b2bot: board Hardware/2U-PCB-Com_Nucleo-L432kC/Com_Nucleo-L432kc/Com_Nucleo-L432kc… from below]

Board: 2 copper layers, 90.0 x 92.0 mm, 41 parts (2 on the bottom side), 42 nets.

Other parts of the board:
QR: LOGO; qr_code_flatsat
SW101: Jumper_RESET_L432KC_Open; SW_PUSH_6mm
SW102: Jumper_MCU_Reset_Open; SW_PUSH_6mm
SW103: Jumper_SX1303_Reset_Open; SW_PUSH_6mm

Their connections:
+3V3: SW103.2; also elsewhere on the board
/L432KC_RESET: SW101.1; also elsewhere on the board
/MCU_NRESET: SW102.1; also elsewhere on the board
/SX1303_RESET: SW103.1; also elsewhere on the board
GND: SW101.2, SW102.2; also elsewhere on the board
